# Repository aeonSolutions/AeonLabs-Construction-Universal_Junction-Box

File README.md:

[Main Catalogue](https://github.com/aeonSolutions/PCB-Prototyping-Catalogue) >> 
[Construction Industry](https://github.com/aeonSolutions/PCB-Prototyping-Catalogue/tree/main/Construction%20Industry)  >>  [
Building & Indoor](https://github.com/aeonSolutions/PCB-Prototyping-Catalogue/tree/main/Construction%20Industry/Building%20%26%20Indoor)

<p align="right">
 <a href="https://github-com.translate.goog/aeonSolutions/PCB-Prototyping-Catalogue/tree/main?_x_tr_sl=en&_x_tr_tl=pt&_x_tr_hl=en&_x_tr_pto=wapp">Change Language</a> <br>
Last update: 30-11-2023
</p>

# AeonLabs Construction Universal Junction Box
Smart Home Light Switch for home automation. Made to fit any universal junction box. Feature Network On/OFF switch. Up to 2 sensors. Connectivity Home CANBus; WiFi, Bluetooth, BLE. This PCB is powered with any 220V AC line.  This LDAD for universal junction box, has already built in CANBUS Network connectivity compatible with ISO 11898-2 for data transmission (and receive) up to 1Mbit/s. Ready to deploy using [Home Assistant](https://www.home-assistant.io/) tools! 

The perfect #PCB for managing construction site works since early construction stages, while, for instance, concreting structural elements. Later on can be left and integrated with any home automation system for active structural and environmental monitoring.

Simple and compatible with existing tools and technologies. Can't get better than this !!! 

*Don't forget to LIKE , SHARE and subscribe the free whatsApp group* and if you liked this PCB consider buying me a cup of coffee. Links below.

### Status
  Waiting for first batch to be tested.

If you already tested this PCB send me a message. Thank you

## Revisions
- revision 1.1
   - added 220V AC Fuse 
  
## Download options
Download this repository if you need the KiCad Files or, download the Gerber files in the release section of this repository

## Liked it ? Get a Free PCB for yourself
Send me your Device or hardware and i will design a custom PCB for it. Free of charge. Contact-me on WhatsApp or email for more info. 

## Q&A WhatsApp Group
If you have any Questions or simply  like this kind of projects and want to stay updated with the latest research ideas and prototypes during the day and week, join the WhatsApp Group
[A.I. Things](https://chat.whatsapp.com/FkNC7u83kuy2QRA5sqjBVg)

## Fully assembled PCB
Alternatively, and if you do not want to build a PCB by yourself and like to buy one:

The price starts at 30eur plus postage fees.
(I will also deliver the assembled PCB with all the components in place at a fair aditonal cost).

#### Be supportive of my dedication and work towards technology education and buy me a coffee. Link below.

________________________________________________________________________________________________________________
## [Go back to main catalogue page](https://github.com/aeonSolutions/PCB-Prototyping-Catalogue)
________________________________________________________________________________________________________________

## PCB Parts list
- DC2DC converter HX4002B x2 : https://s.click.aliexpress.com/e/_Ak7IPx
- Capacitor 100nF SMD 1206 : https://s.click.aliexpress.com/e/_AVdmzr
- Capacitor 2.2uF SMD 1206 : https://s.click.aliexpress.com/e/_AVdmzr
- Resistor SMD 1206 330R x3 : https://s.click.aliexpress.com/e/_A7OXrR
- ESP32 WROOM32 x1 : https://s.click.aliexpress.com/e/_AF7N6l
- KF350 Screw pitch 3.5mm Straight 3 Pin pcb terminal block : https://s.click.aliexpress.com/e/_AChDnp

- This PCB connects with the DS18b20 Temperature sensor : https://s.click.aliexpress.com/e/_AWDAMr 

## PCB Enclosure
The enclosure for this PCB can be bought online by searching for [Univerdal Junction Box 60x60]() .

## Firmware Download 
one can use the PCB in the repository [AeonLabs-MCU-Burner-USB-to-UART-TTL](https://github.com/aeonSolutions/AeonLabs-MCU-Burner-USB-to-UART-TTL) to program the ESP32 WROOM32 MCU on this PCB.

<br>

## Author

You can get in touch with me on my LinkedIn Profile:

#### Miguel Tomas

You can also follow my GitHub Profile to stay updated about my latest projects: 

<br>

### Be supportive of my dedication and work towards technology education and buy me a cup of coffee
The PCB Desgin Files i provide here for anyone to use are free. If you like this Smart Device or use it, please consider buying me a cup of coffee, a slice of pizza or a book to help me study, eat and think new PCB design files.

<br />

### Make a donation on Paypal
Make a donation on paypal and get a TAX refund*.

<br>

### Support all these open hardware projects and become a patreon  
Liked any of my PCB KiCad Designs? Help and Support my open work to all by becomming a LDAD Patreon.
In return I will give a free PCB design in KiCad to all patreon supporters. To learn more go to patreon.com. Link below.

#

### License

Before proceeding to download any of AeonLabs software solutions for open-source development and/or PCB hardware electronics solutions for open-hardware development make sure you are choosing the right license for your project. See [AeonLabs Solutions for Open Hardware & Source Development](https://github.com/aeonSolutions/PCB-Prototyping-Catalogue/wiki/AeonLabs-Solutions-for-Open-Hardware-&-Source-Development) for more information. 

### Be supportive of my dedication and work towards technology education and buy me a coffee

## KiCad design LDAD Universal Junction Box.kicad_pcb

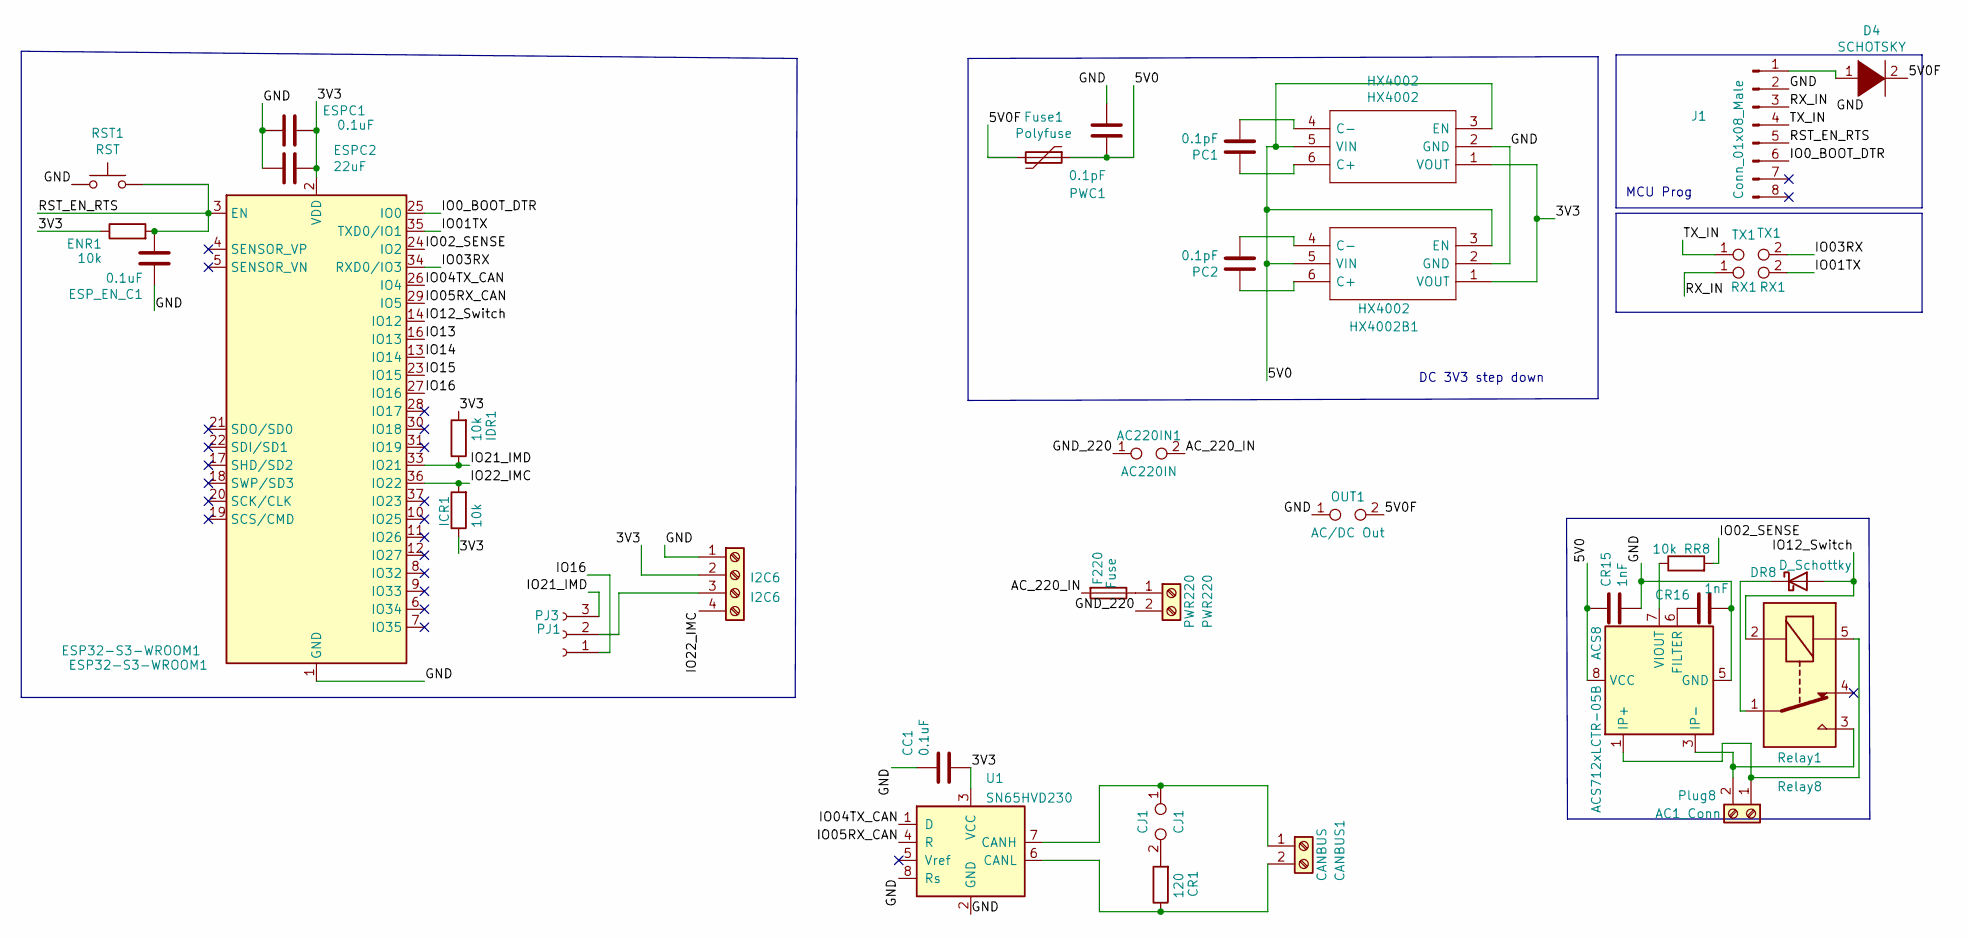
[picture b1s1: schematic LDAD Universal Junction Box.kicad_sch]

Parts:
AC220IN1: AC220IN; TestPoint_2Pads_Pitch3.81mm_Drill1.3mm
ACS8: ACS712xLCTR-05B; SOIC-8_3.9x4.9mm_P1.27mm
CANBUS1: CANBUS; TerminalBlock_bornier-2_P5.08mm
CC1: 0.1uF; C_1206_3216Metric_Pad1.33x1.80mm_HandSolder
CJ1: CJ1; TestPoint_2Pads_Pitch2.54mm_Drill0.8mm
CR1: 120; R_1206_3216Metric_Pad1.30x1.75mm_HandSolder
CR15, CR16: 1nF; C_1206_3216Metric
D4: SCHOTSKY; D_1210_3225Metric_Pad1.42x2.65mm_HandSolder
DR8: D_Schottky; D_1210_3225Metric_Pad1.42x2.65mm_HandSolder
ENR1: 10k; R_1206_3216Metric_Pad1.30x1.75mm_HandSolder
ESP32-S3-WROOM1: ESP32-S3-WROOM1; ESP32-WROOM-32
ESPC1: 0.1uF; C_1206_3216Metric_Pad1.33x1.80mm_HandSolder
ESPC2: 22uF; C_1206_3216Metric_Pad1.33x1.80mm_HandSolder
ESP_EN_C1: 0.1uF; C_1206_3216Metric_Pad1.33x1.80mm_HandSolder
F220: Fuse; Fuse_Bourns_MF-RG300
Fuse1: Polyfuse; Fuse_1206_3216Metric_Pad1.42x1.75mm_HandSolder
HX4002, HX4002B1: HX4002; HX4002 SOT95 P280X125-6N; Manufacturer_Part_Number HX4002
I2C6: I2C6; TerminalBlock_4Ucon_1x04_P3.50mm_Vertical
ICR1: 10k; R_1206_3216Metric_Pad1.30x1.75mm_HandSolder
IDR1: 10k; R_1206_3216Metric_Pad1.30x1.75mm_HandSolder
J1: Conn_01x08_Male; SOIC_clipProgSmall
OUT1: AC/DC Out; TestPoint_2Pads_Pitch2.54mm_Drill0.8mm
PC1, PC2: 0.1pF; C_1206_3216Metric_Pad1.33x1.80mm_HandSolder
PJ3: PJ1; TestPoint_3Pads_Pitch2.54mm_Drill0.8mm
PWC1: 0.1pF; C_1206_3216Metric_Pad1.33x1.80mm_HandSolder
PWR220: PWR220; TerminalBlock_bornier-2_P5.08mm
Plug8: AC1_Conn; TerminalBlock_bornier-2_P5.08mm
RR8: 10k; R_1206_3216Metric
RST1: RST; SW_Push_SPST_NO_Alps_SKRK AliExpress
RX1: RX1; TestPoint_Pad_Bridge_1.0x1.0mm
Relay8: Relay1; Relay_SPDT_SANYOU_SRD_Series_Form_C
TX1: TX1; TestPoint_Pad_Bridge_1.0x1.0mm
U1: SN65HVD230; SOIC-8_3.9x4.9mm_P1.27mm

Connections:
/3V3: CC1.2, ENR1.1, ESP32-S3-WROOM1.2 (VDD), ESPC1.1, ESPC2.1, HX4002.1 (VOUT), HX4002B1.1 (VOUT), I2C6.2, ICR1.1, IDR1.2, U1.3 (VCC)
/5V0: ACS8.8 (VCC), CR15.1, Fuse1.1, HX4002.3 (EN), HX4002.5 (VIN), HX4002B1.3 (EN), HX4002B1.5 (VIN), PWC1.1
/5V0F: D4.2 (A), Fuse1.2, OUT1.2
/AC_220_IN: AC220IN1.2, F220.2
/GND: ACS8.5 (GND), CC1.1, CR15.2, CR16.2, ESP32-S3-WROOM1.1 (GND), ESP32-S3-WROOM1.15 (GND), ESP32-S3-WROOM1.38 (GND), ESP32-S3-WROOM1.39 (GND), ESPC1.2, ESPC2.2, ESP_EN_C1.1, HX4002.2 (GND), HX4002B1.2 (GND), I2C6.1, J1.2, OUT1.1, PWC1.2, RST1.1, U1.2 (GND), U1.8 (Rs)
/GND_220: AC220IN1.1, PWR220.2
/IO0_BOOT_DTR: ESP32-S3-WROOM1.25 (IO0), J1.6
/IO01TX: ESP32-S3-WROOM1.35 (TXD0/IO1), RX1.2
/IO02_SENSE: ESP32-S3-WROOM1.24 (IO2), RR8.2
/IO03RX: ESP32-S3-WROOM1.34 (RXD0/IO3), TX1.2
/IO04TX_CAN: ESP32-S3-WROOM1.26 (IO4), U1.1 (D)
/IO05RX_CAN: ESP32-S3-WROOM1.29 (IO5), U1.4 (R)
/IO12_Switch: DR8.2 (A), ESP32-S3-WROOM1.14 (IO12), Relay8.2
/IO13: ESP32-S3-WROOM1.16 (IO13)
/IO14: ESP32-S3-WROOM1.13 (IO14)
/IO15: ESP32-S3-WROOM1.23 (IO15)
/IO16: ESP32-S3-WROOM1.27 (IO16), PJ3.1
/IO21_IMD: ESP32-S3-WROOM1.33 (IO21), IDR1.1, PJ3.3
/IO22_IMC: ESP32-S3-WROOM1.36 (IO22), I2C6.4, ICR1.2
/RST_EN_RTS: ENR1.2, ESP32-S3-WROOM1.3 (EN), ESP_EN_C1.2, J1.5, RST1.2
/RX_IN: J1.3, RX1.1
/TX_IN: J1.4, TX1.1
unnamed: ACS8.1 (IP+), ACS8.2 (IP+), Plug8.1, Relay8.5
unnamed: ACS8.3 (IP-), ACS8.4 (IP-), Plug8.2, Relay8.3
unnamed: ACS8.6 (FILTER), CR16.1
unnamed: ACS8.7 (VIOUT), RR8.1
unnamed: CANBUS1.1, CJ1.1, U1.7 (CANH)
unnamed: CANBUS1.2, CR1.1, U1.6 (CANL)
unnamed: CJ1.2, CR1.2
unnamed: D4.1 (K), J1.1
unnamed: DR8.1 (K), Relay8.1
unnamed: F220.1, PWR220.1
unnamed: HX4002.4 (C-), PC1.2
unnamed: HX4002.6 (C+), PC1.1
unnamed: HX4002B1.4 (C-), PC2.2
unnamed: HX4002B1.6 (C+), PC2.1
unnamed: I2C6.3, PJ3.2

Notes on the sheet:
DC 3V3 step down
MCU Prog

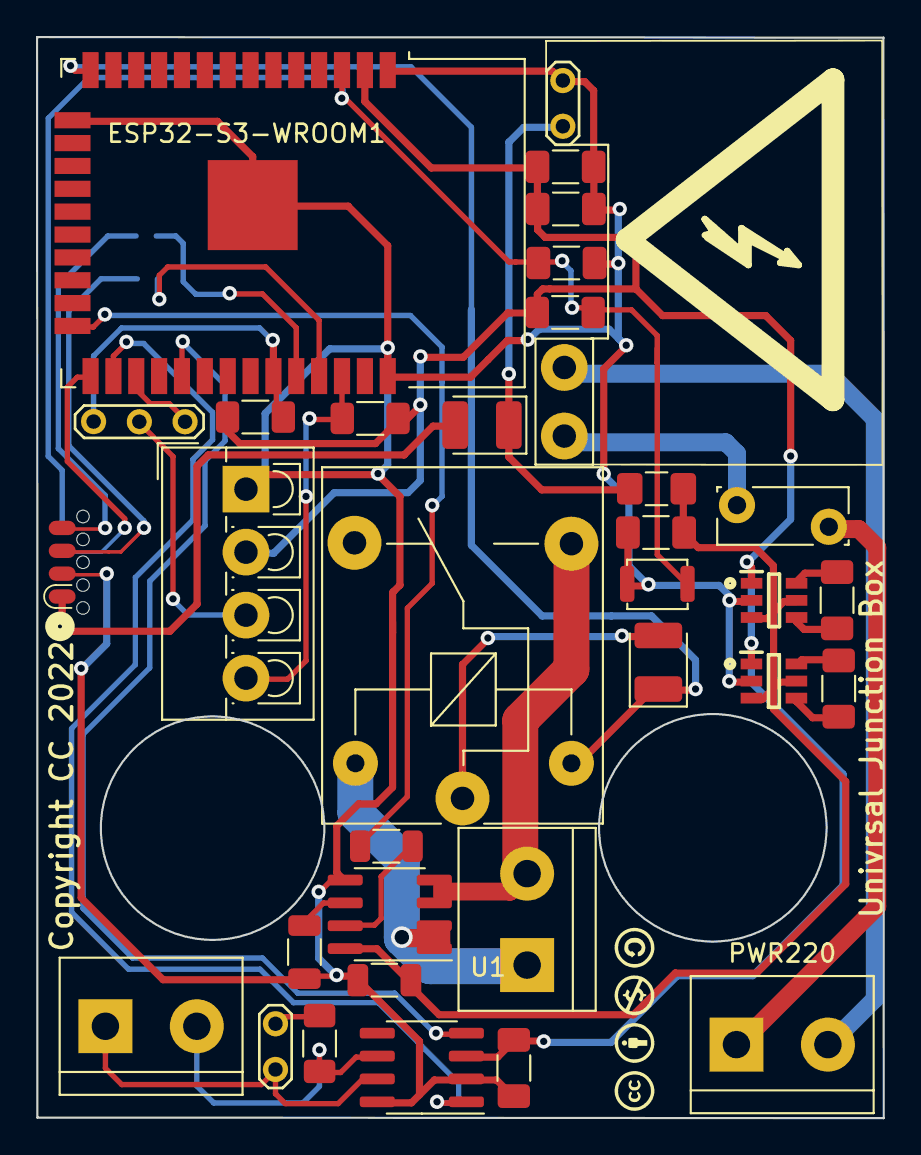
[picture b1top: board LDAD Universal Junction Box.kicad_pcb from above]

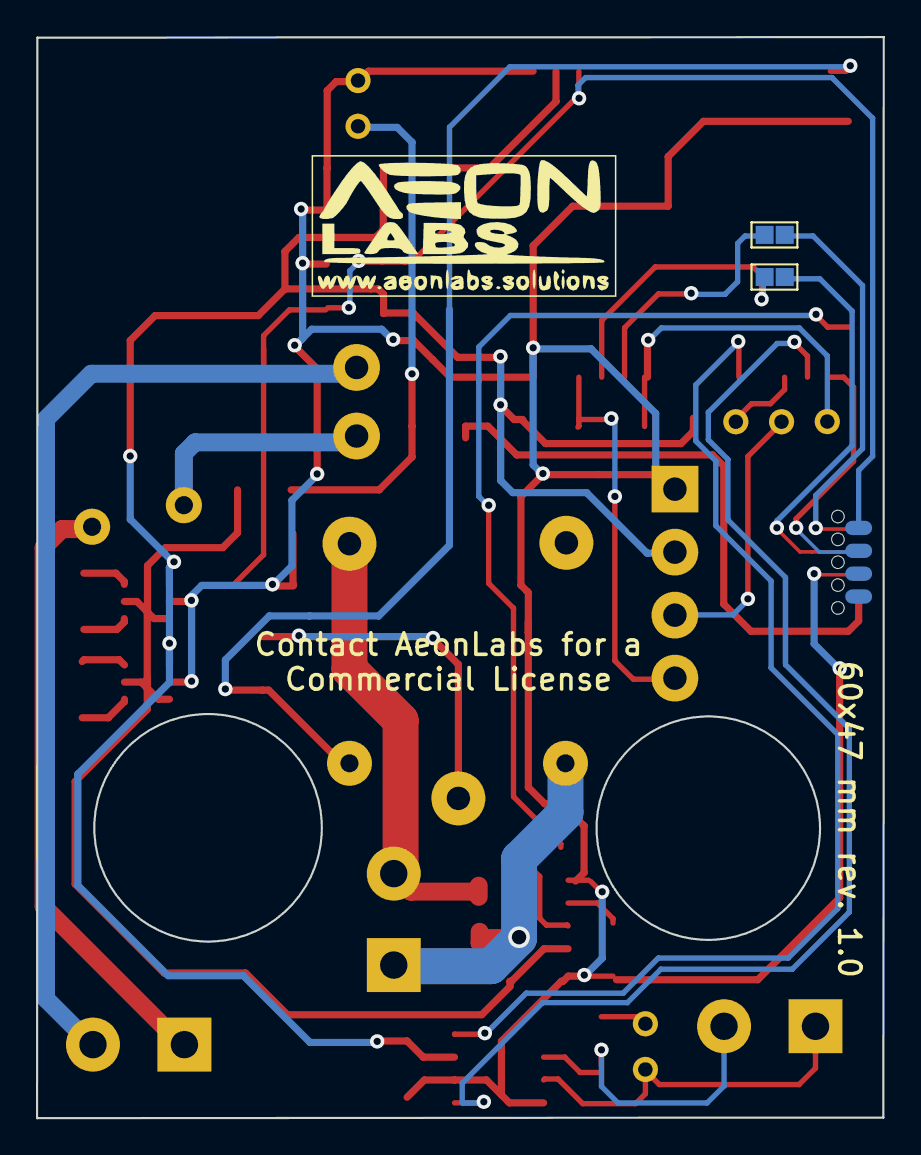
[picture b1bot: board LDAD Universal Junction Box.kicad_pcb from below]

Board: 2 copper layers, 47.0 x 60.1 mm, 36 parts (2 on the bottom side), 34 nets.

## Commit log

2022-06-06 revision 1.0

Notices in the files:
LDAD Universal Junction Box.kicad_pcb:
Copyright CC 2022
